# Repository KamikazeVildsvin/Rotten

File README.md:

# Rotten - DIY Pro Co RAT Clone
This repository contains the KiCad files for a DIY clone of the classic Pro Co RAT distortion effect pedal.
The schematic is an implementation of the one found on [ElectroSmash](https://www.electrosmash.com/proco-rat), so a big shout-out to them.
The article on [ElectroSmash](https://www.electrosmash.com/proco-rat) has a great description of the functionality of the circuit.

## Interactive BOM
An [interactive HTML BOM](https://html-preview.github.io/?url=https://github.com/KamikazeVildsvin/Rotten/blob/master/PCB/Rotten/bom/ibom.html) can be found in the `PCB/Rotten/bom` directory.
This can be used as a tool to easier populate the PCB.

## Images
### Schematic

### PCB

### 3D Model

# Wiring
## Footswitch - True Bypass Wiring
You will need a 3PDT type switch in order to wire things correctly. 
The six connections on the PCB needs to be wired to the switch as indicated by the image below.

*source: https://support.banzaimusic.com/article/53-true-bypass-switch-wiring*

I would recommend that you use the interactive BOM above to see what connection on the PCB matches the correct pin on the footswitch, since the silkscreen is very small and probably not readable on the actual physical PCB.

*NOTE*: If you don't want to use the LED indicator, you can disregard the **GROUND** and **LED** connections on the footswitch and don't solder these connections to the PCB.

## Potentiometers
The PCB has been designed so pin 1, 2, and 3 on the board matches the pinout of the 100k Potentiometers.
This means that pin 1 on the potentiometer should go to the square pad on the PCB, as indicated below.

## Jack Connectors
The Jack connectors (both the 1/4" audio jacks and the DC jack) only needs two connections.
For the audio jacks, pin 1 should be soldered to the tib of the connector and the sleeve to pin 2.
The silkscreen on the PCB also indicates which pad is ground or the signal, as can be seen below

The DC barrek jack needs to be connected center negatic in order for the effect to work with standard stompbox power supplies.
This means that you should connect the tip to ground and the **+9V** to the sleeve of the barrel jack connector.

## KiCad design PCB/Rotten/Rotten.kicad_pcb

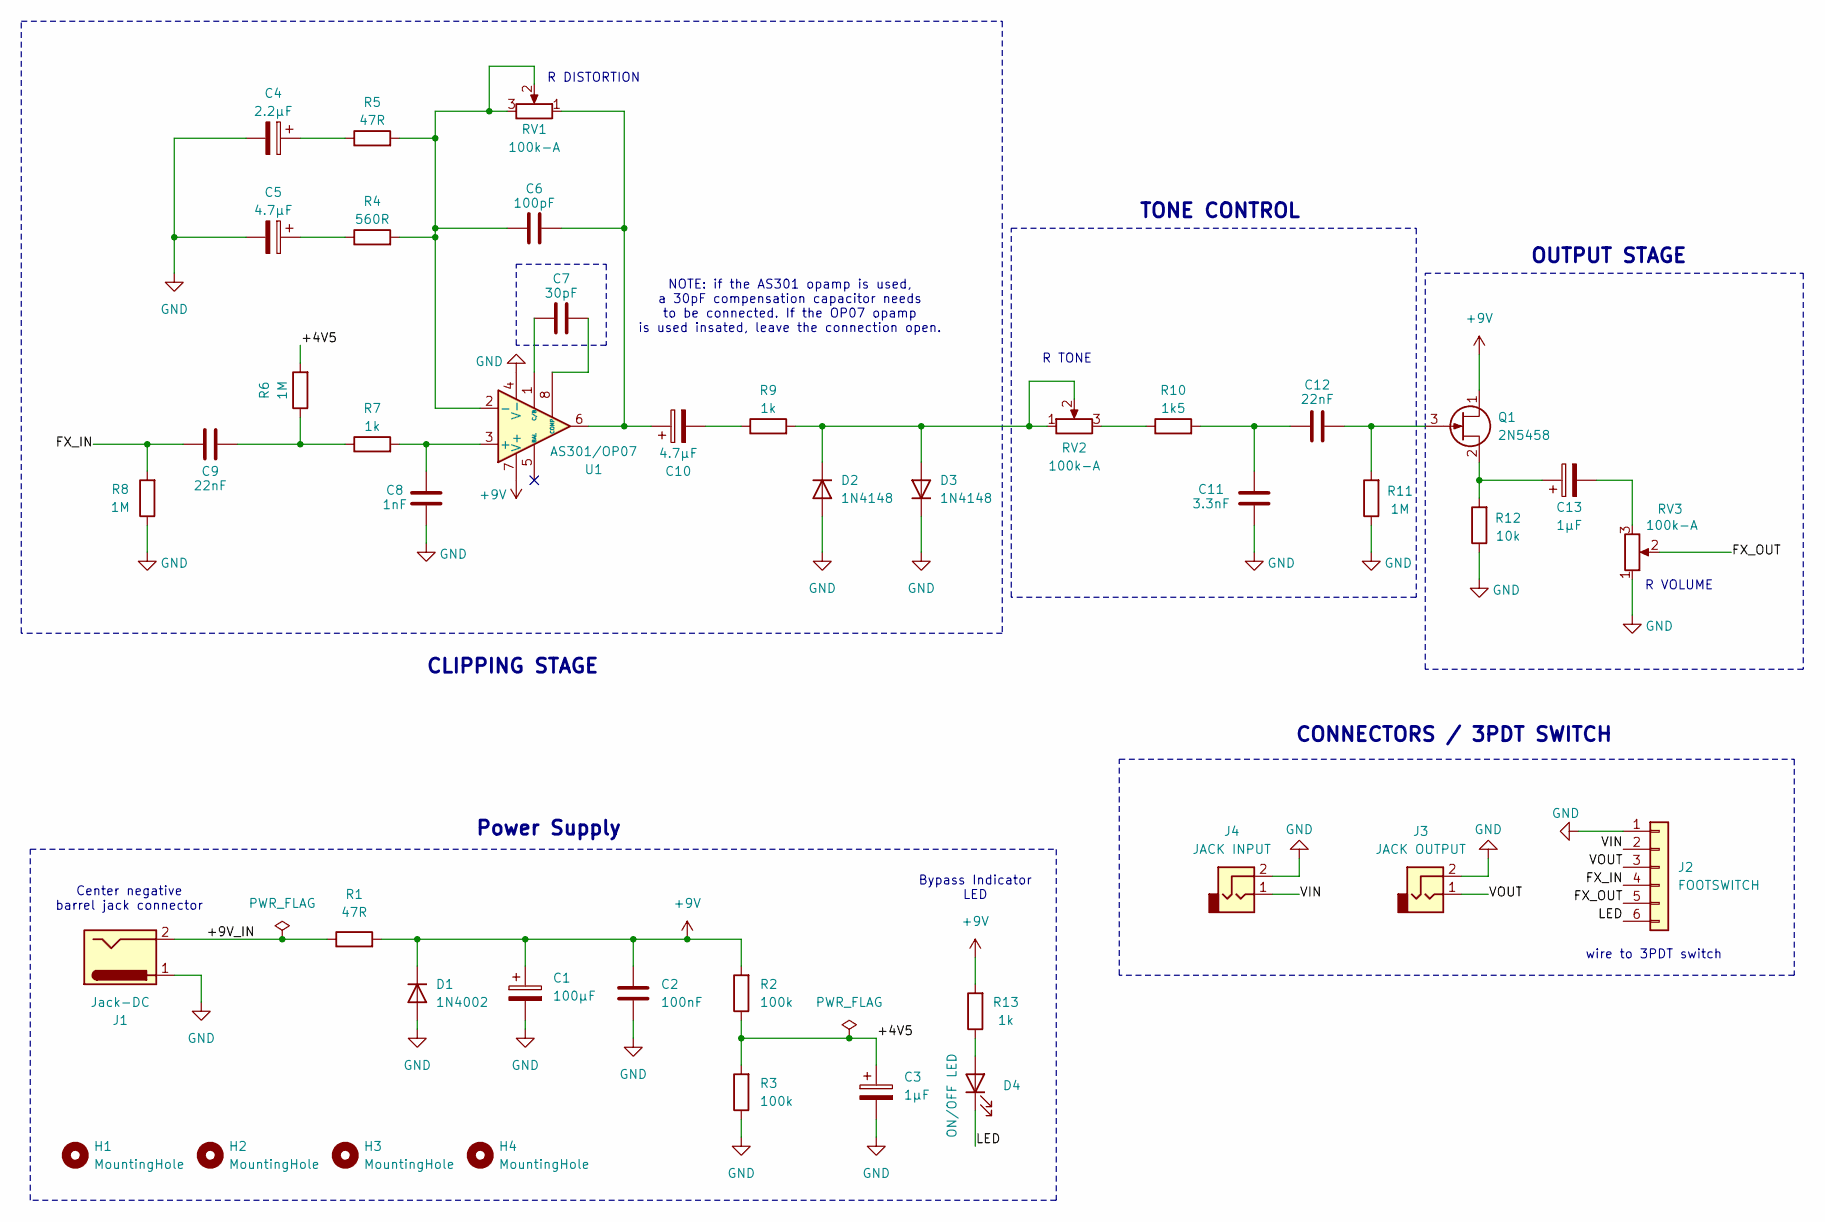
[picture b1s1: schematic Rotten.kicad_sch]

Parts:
C1: 100µF; CP_Radial_D6.3mm_P2.50mm
C2: 100nF; C_Disc_D4.3mm_W1.9mm_P5.00mm
C3, C13: 1µF; CP_Radial_D5.0mm_P2.00mm
C4: 2.2µF; CP_Radial_D5.0mm_P2.00mm
C5, C10: 4.7µF; CP_Radial_D5.0mm_P2.00mm
C6: 100pF; C_Disc_D4.3mm_W1.9mm_P5.00mm
C7: 30pF; C_Disc_D4.3mm_W1.9mm_P5.00mm
C8: 1nF; C_Disc_D4.3mm_W1.9mm_P5.00mm
C9, C12: 22nF; C_Disc_D4.3mm_W1.9mm_P5.00mm
C11: 3.3nF; C_Disc_D4.3mm_W1.9mm_P5.00mm
D1: 1N4002; D_DO-41_SOD81_P10.16mm_Horizontal
D2, D3: 1N4148; D_DO-41_SOD81_P10.16mm_Horizontal
D4: ON/OFF LED; LED_D5.0mm_IRBlack
H1, H2, H3, H4: MountingHole; MountingHole_3.2mm_M3_DIN965
J1: Jack-DC; PinHeader_1x02_P2.54mm_Vertical
J2: FOOTSWITCH; PinHeader_1x06_P2.54mm_Vertical
J3: JACK OUTPUT; PinHeader_1x02_P2.54mm_Vertical
J4: JACK INPUT; PinHeader_1x02_P2.54mm_Vertical
Q1: 2N5458; TO-92
R1, R5: 47R; R_Axial_DIN0207_L6.3mm_D2.5mm_P7.62mm_Horizontal
R2, R3: 100k; R_Axial_DIN0207_L6.3mm_D2.5mm_P7.62mm_Horizontal
R4: 560R; R_Axial_DIN0207_L6.3mm_D2.5mm_P7.62mm_Horizontal
R6, R8, R11: 1M; R_Axial_DIN0207_L6.3mm_D2.5mm_P7.62mm_Horizontal
R7, R9, R13: 1k; R_Axial_DIN0207_L6.3mm_D2.5mm_P7.62mm_Horizontal
R10: 1k5; R_Axial_DIN0207_L6.3mm_D2.5mm_P7.62mm_Horizontal
R12: 10k; R_Axial_DIN0207_L6.3mm_D2.5mm_P7.62mm_Horizontal
RV1, RV2, RV3: 100k-A; PinSocket_1x03_P2.54mm_Vertical
U1: AS301/OP07; DIP-8_W7.62mm_Socket

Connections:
+9V: C1.1, C2.1, D1.1 (K), Q1.1 (D), R1.2, R2.2, R13.2, U1.7 (V+)
/+4V5: C3.1, R2.1, R3.2, R6.2
/+9V_IN: J1.2, R1.1
/FX_IN: C9.1, J2.4, R8.2
/FX_OUT: J2.5, RV3.2
/LED: D4.1 (K), J2.6
/VIN: J2.2, J4.1
/VOUT: J2.3, J3.1
GND: C1.2, C2.2, C3.2, C4.2, C5.2, C8.2, C11.2, D1.2 (A), D2.2 (A), D3.1 (K), J1.1, J2.1, J3.2, J4.2, R3.1, R8.1, R11.1, R12.1, RV3.1, U1.4 (V-)
unnamed: C4.1, R5.1
unnamed: C5.1, R4.1
unnamed: C9.2, R6.1, R7.1
unnamed: C6.1, C10.1, RV1.1, U1.6
unnamed: C10.2, R9.1
unnamed: C11.1, C12.1, R10.2
unnamed: C13.2, RV3.3
unnamed: D2.1 (K), D3.2 (A), R9.2, RV2.1, RV2.2
unnamed: D4.2 (A), R13.1
unnamed: C12.2, Q1.3 (G), R11.2
unnamed: C13.1, Q1.2 (S), R12.2
unnamed: R10.1, RV2.3
unnamed: C8.1, R7.2, U1.3 (+)
unnamed: C6.2, R4.2, R5.2, RV1.2, RV1.3, U1.2 (-)
unnamed: C7.1, U1.8 (COMP)
unnamed: C7.2, U1.1 (C/B)

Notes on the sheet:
TONE CONTROL
Power Supply
R VOLUME
CLIPPING STAGE
wire to 3PDT switch
NOTE: if the AS301 opamp is used, a 30pF compensation capacitor needs to be connected. If the OP07 opamp is used insated, leave the connection open.
R DISTORTION
Bypass Indicator LED
OUTPUT STAGE
CONNECTORS / 3PDT SWITCH
Center negative barrel jack connector
R TONE

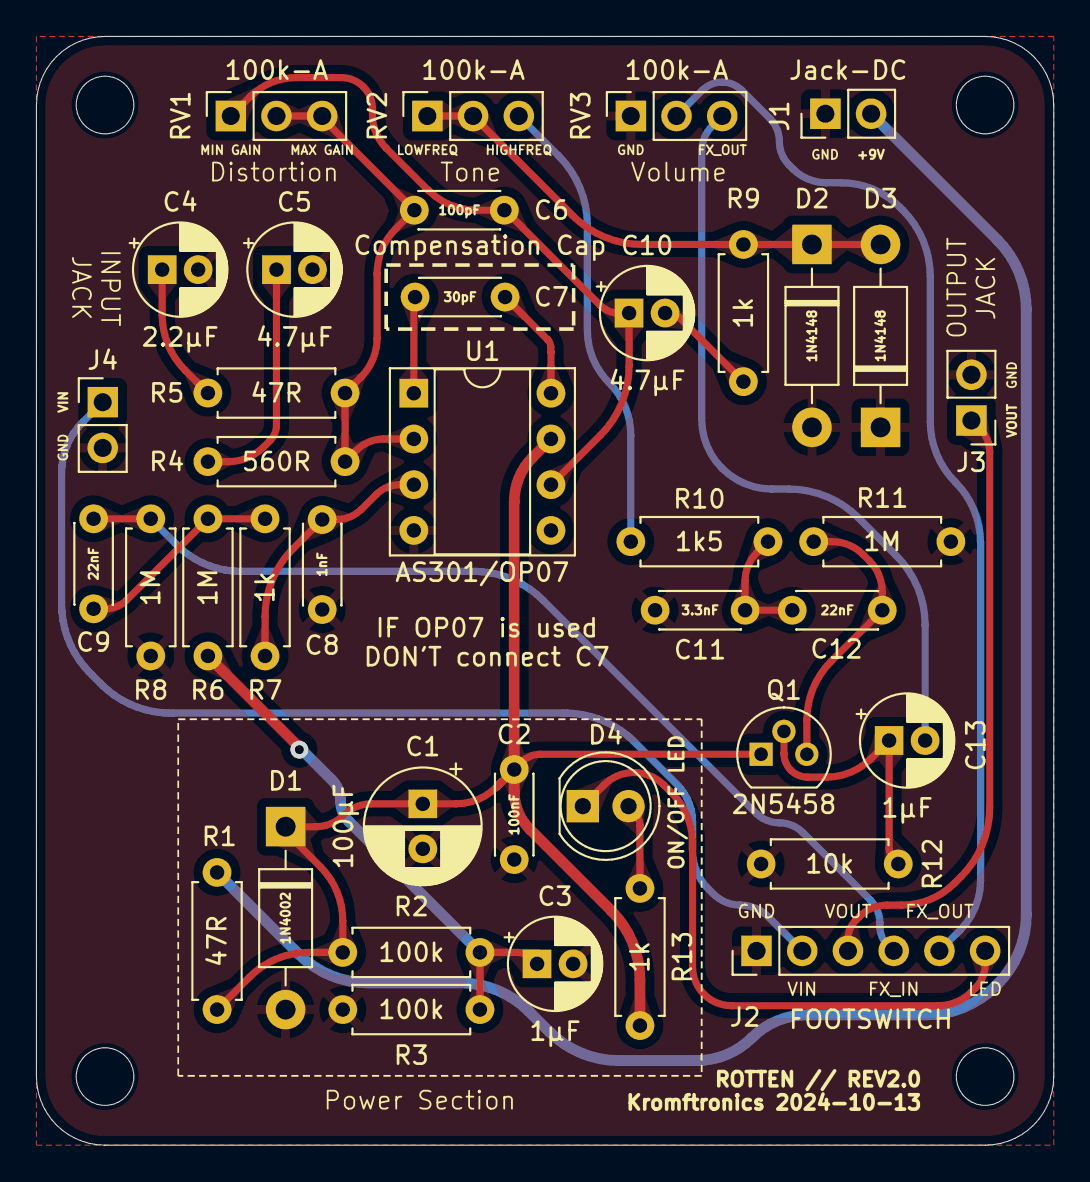
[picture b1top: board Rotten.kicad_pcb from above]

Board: 2 copper layers, 56.5 x 61.6 mm, 43 parts (0 on the bottom side), 25 nets.

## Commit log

2024-06-05 created README
2024-06-05 Create LICENSE
2024-06-05 created .gitignore. Created KiCad project
2024-06-05 created schematic. Imported footprints into PCBNew
2024-06-06 created rev1 layout and added images
2024-06-06 Addd pictures to README
2024-06-06 saved files
2024-06-07 added ElectroSmash citation to README. Added pdf of the schematic.
2024-06-07 renamed rev1 schematic pdf
2024-06-07 added png version of rev1 schematic
2024-06-07 Added schematic png to README
2024-06-08 changed clipping diodes to 1N4148. Updated schematic and PCB images. Generated an HTML BOM.
2024-06-08 Update README.md with link and description of the interactive BOM
2024-10-12 Added footswitch wiring image and description to README. Added note about wrong LED circuit.
2024-10-12 Updated README with better description of the footswitch wiring.
2024-10-13 Created Rev2 update! Fixed LED footswitch error that resulted in no light. Flipped "volume" and "gain" connections on PCB (1 -> 3). Fixed wrong pinout on JFET that resulted in no audio. Updated READM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
2024-10-13 rotated jack connection image
2024-10-13 generated new ibom for rev2.
2024-12-22 Added variable revision and issue date on the silkscreen, so I don't forget to update the rev and issue date on the silkscreen.
